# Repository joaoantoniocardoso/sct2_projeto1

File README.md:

# sct2_projeto1
Primeiro projeto de controlador digital da disciplina de Sistemas de Controles 2

Relatório: [Relatorio.pdf](Relatorio.pdf)

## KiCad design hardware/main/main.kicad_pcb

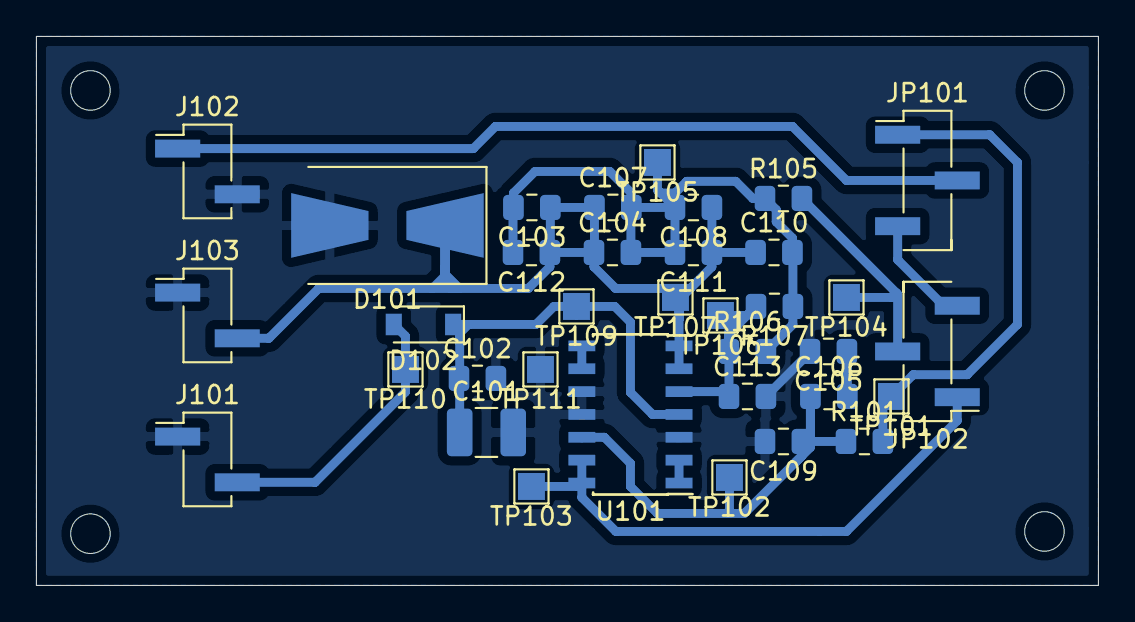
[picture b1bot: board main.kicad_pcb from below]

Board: 2 copper layers, 59.0 x 30.5 mm, 39 parts (35 on the bottom side), 15 nets.

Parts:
C101: 10u; C_1210_3225Metric_Pad1.42x2.65mm_HandSolder
C102, C103, C104, C105, C106, C107, C108, C109, C110, C111, C112, C113: 100n; C_0805_2012Metric_Pad1.15x1.40mm_HandSolder
D101: D_Zener_Small; D_SMB-SMC_Universal_Handsoldering
D102: 1N4148W; D_SOD-123
H101, H102, H103, H104: MountingHole; MountingHole_2.2mm_M2
J101, J102, J103: Conn_01x02_Female; PinHeader_1x02_P2.54mm_Vertical_SMD_Pin1Left
JP101, JP102: SolderJumper_3_Open; PinHeader_1x03_P2.54mm_Vertical_SMD_Pin1Left
R101: 10k; R_0805_2012Metric_Pad1.15x1.40mm_HandSolder
R105: 68k; R_0805_2012Metric_Pad1.15x1.40mm_HandSolder
R106: 33k; R_0805_2012Metric_Pad1.15x1.40mm_HandSolder
R107: 39k; R_0805_2012Metric_Pad1.15x1.40mm_HandSolder
TP101, TP102, TP103, TP104, TP105, TP106, TP107, TP109, TP110, TP111: TestPoint; TestPoint_Pad_1.5x1.5mm
U101: LM324; SOIC-14_3.9x8.7mm_P1.27mm

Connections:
+5V: C101.1, C102.1, D102.1, TP109.1, U101.4
/INPUT: J102.1, JP101.2
/MIDDLE: JP102.2, R105.2, TP104.1
/OUTPUT: C103.1, C104.1, C107.1, C108.1, C110.1, C111.1, C112.1, D101.1, J103.2, TP107.1, U101.6, U101.7
GND: C101.2, C102.2, C105.2, C109.2, C113.2, D101.2, J101.1, J102.2, J103.1, TP111.1, U101.3, U101.10, U101.11
unnamed: C103.2, C104.2, C107.2, C108.2, C110.2, C111.2, C112.2, R105.1, R106.2, R107.1, TP105.1
unnamed: C105.1, C106.2
unnamed: C106.1, C109.1, R101.1, TP102.1, U101.12
unnamed: C113.1, R106.1, R107.2, TP106.1, U101.5
unnamed: D102.2, J101.2, TP110.1
unnamed: JP101.1, R101.2, TP101.1
unnamed: JP101.3, JP102.3
unnamed: JP102.1, TP103.1, U101.13, U101.14
unnamed: U101.1, U101.2
unnamed: U101.8, U101.9

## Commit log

2019-04-03 Planta adicionada, mas contém erros:
    O principal erro detectado é que para utilizar alimentação simples, a topologia
    do bloco de primeira ordem deve ser alterada, no caso deste commit a
    topologia ainda não foi alterada.
2019-04-03 Circuito modificado para alimentação simples.
2019-04-03 Simulação da topologia de alimentação simples e sua equivalencia com a topologia inicialmente proposta pelo professor
2019-04-03 Nenhum ganho é necessário na estrutura para ser equivalente. A análise em freq. estava errada.
2019-04-03 PCB updated to single supply topology
2019-04-03 ERC -> ok
2019-04-03 Firmware inicial adicionado.
2019-04-03 Painel plotado para confecção da placa por transferência térmica
2019-04-03 simulação atualizada
2019-05-27 Finalizado
